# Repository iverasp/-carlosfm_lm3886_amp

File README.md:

## LM3886 amplifier

This PCB is for an LM3886 amplifier, based on schematics by Carlos.  
Pin 11 is removed to allow routing.

### Dimensions of parts

100nF caps: 15mm spacing, 18x5.5mm L x W  
2200uF caps: 7.5mm spacing, 18mm diameter  
3.3nF caps: 7.5mm spacing, 10x3mm L x W  
3.3uF caps: 22.5mm spacing, 26.5x11mm L x W  
330pF cap: 5mm spacing, 7.5x4mm L x W  

1W resistors: L=10mm (raised above PCB to provide cooling)  
other resistors: L=10mm

### Remaining parts

Feedback resistor (2k) is placed on chip terminals (3, 9)  
Resistor RM (10k) is placed on chip terminals (8, 4)  
Short the pads A1 and A2 using a wire  
The 2.2uF input cap is too big to fit on the board. Place it and the 15k resistor somewhere convenient instead (e.g. on the RCA connector)  
The Zobel network is placed on the speaker terminals

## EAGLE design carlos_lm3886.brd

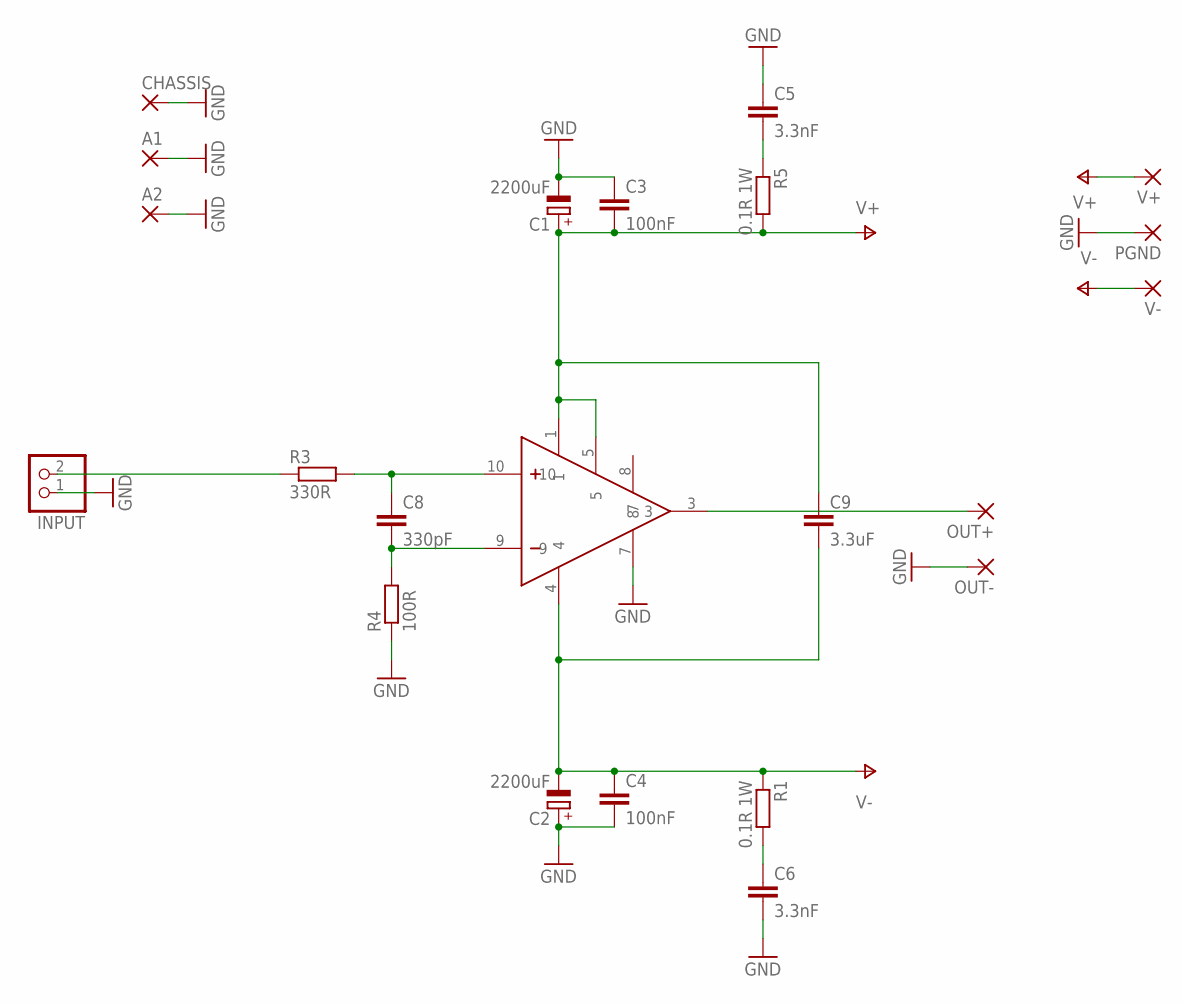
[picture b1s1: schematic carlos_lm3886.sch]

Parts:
A1, A2: 2,54/1,0
C1, C2: 2200uF; E7,5-18
C3, C4: 100nF; C150-054X183
C5, C6: 3.3nF; C075-032X103
C8: 330pF; C050-045X075
C9: 3.3uF; C225-087X268
CHASSIS: 2,54/1,0
INPUT: PINHD-1X2; 1X02
OUT+: 2,54/1,0
OUT-: 2,54/1,0
PGND: 2,54/1,0
R1, R5: 0.1R 1W; 0309/10
R3: 330R; 0207/10
R4: 100R; 0207/10
U$1: LM3886T; TO220-11
V+: 2,54/1,0
V-: 2,54/1,0

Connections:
GND: A1.1, A2.1, C1.-, C2.+, C3.1, C4.2, C5.1, C6.2, CHASSIS.1, INPUT.1, OUT-.1, PGND.1, R4.1, U$1.7
unnamed: INPUT.2, R3.1
unnamed: C6.1, R1.2
unnamed: C5.2, R5.1
unnamed: C8.1, R3.2, U$1.10
unnamed: C8.2, R4.2, U$1.9
unnamed: OUT+.1, U$1.3
V+: C1.+, C3.2, C9.1, R5.2, U$1.1, U$1.5, V+.1
V-: C2.-, C4.1, C9.2, R1.1, U$1.4, V-.1

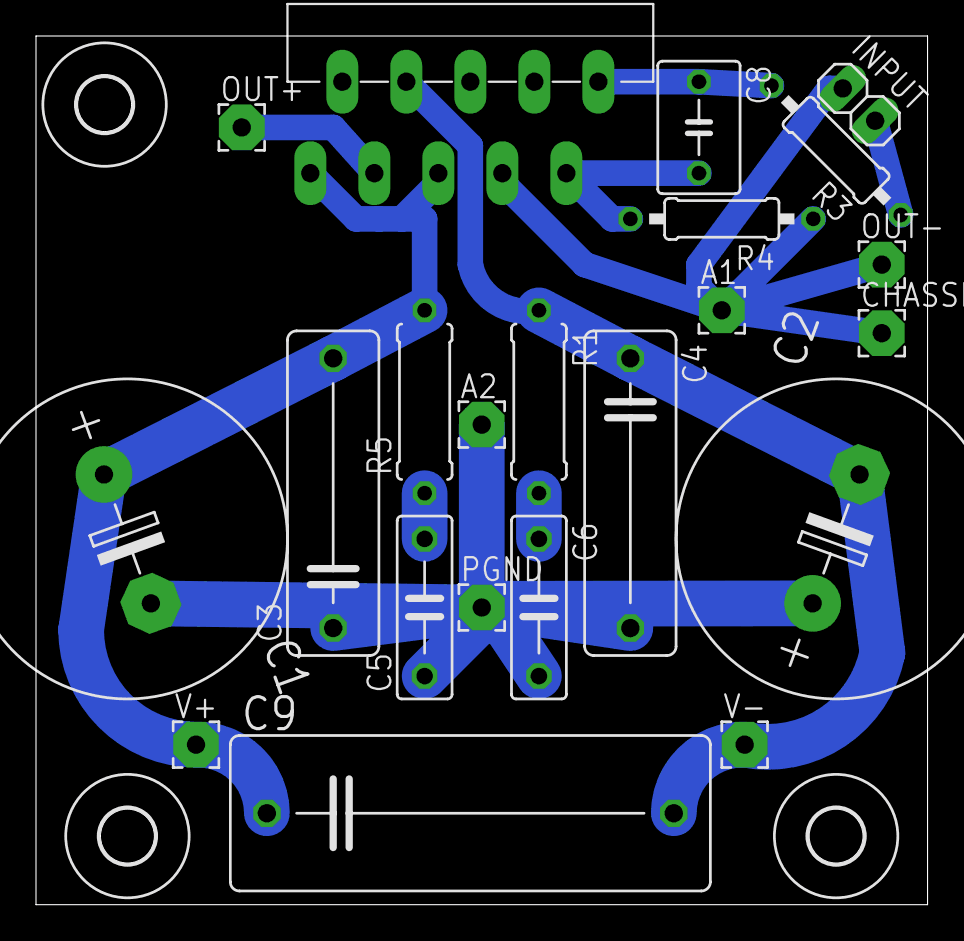
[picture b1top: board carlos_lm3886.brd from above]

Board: 2 copper layers, 49.5 x 48.3 mm, 25 parts (0 on the bottom side), 9 nets.

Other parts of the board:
U$2, U$3, U$4: 3,0

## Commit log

2016-09-24 schematic completed
2016-09-24 added readme
2016-09-24 layout without traces completed
2016-09-26 final?
